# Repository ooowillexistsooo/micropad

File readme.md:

# micropad

the silly little micropad

## bill of materials
- 4 keys
- 4 keycaps
- pcb <3 ofc
- the board attatchment thing
- [the complete bom](production/bom.csv)

## where the things are
- the gerbers are in production/gerbils
- gerber zip is production/gerbils/gerbils.zip
- firmware is in production/firmware (obviously)
- the print file is production/cad/3d-print-this.stl
- the step file is production/cad/hackpad-XD.step (i hope)

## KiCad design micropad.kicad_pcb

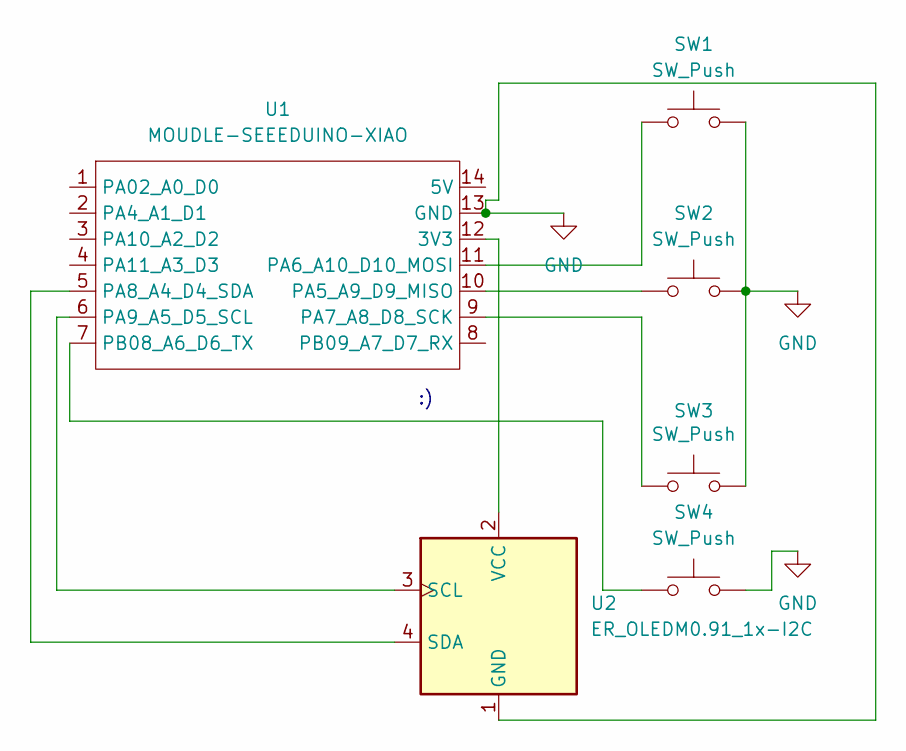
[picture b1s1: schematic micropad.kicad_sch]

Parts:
SW1, SW2, SW3, SW4: SW_Push; SW_Cherry_MX_1.00u_PCB
U1: MOUDLE-SEEEDUINO-XIAO; XIAO-Generic-Hybrid-14P-2.54-21X17.8MM
U2: ER_OLEDM0.91_1x-I2C

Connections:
GND: SW1.2, SW2.2, SW3.2, SW4.2, U1.13 (GND), U2.1 (GND)
unnamed: U1.12 (3V3), U2.2 (VCC)
unnamed: SW2.1, U1.10 (PA5_A9_D9_MISO)
unnamed: SW1.1, U1.11 (PA6_A10_D10_MOSI)
unnamed: SW3.1, U1.9 (PA7_A8_D8_SCK)
unnamed: U1.5 (PA8_A4_D4_SDA), U2.4 (SDA)
unnamed: U1.6 (PA9_A5_D5_SCL), U2.3 (SCL)
unnamed: SW4.1, U1.7 (PB08_A6_D6_TX)

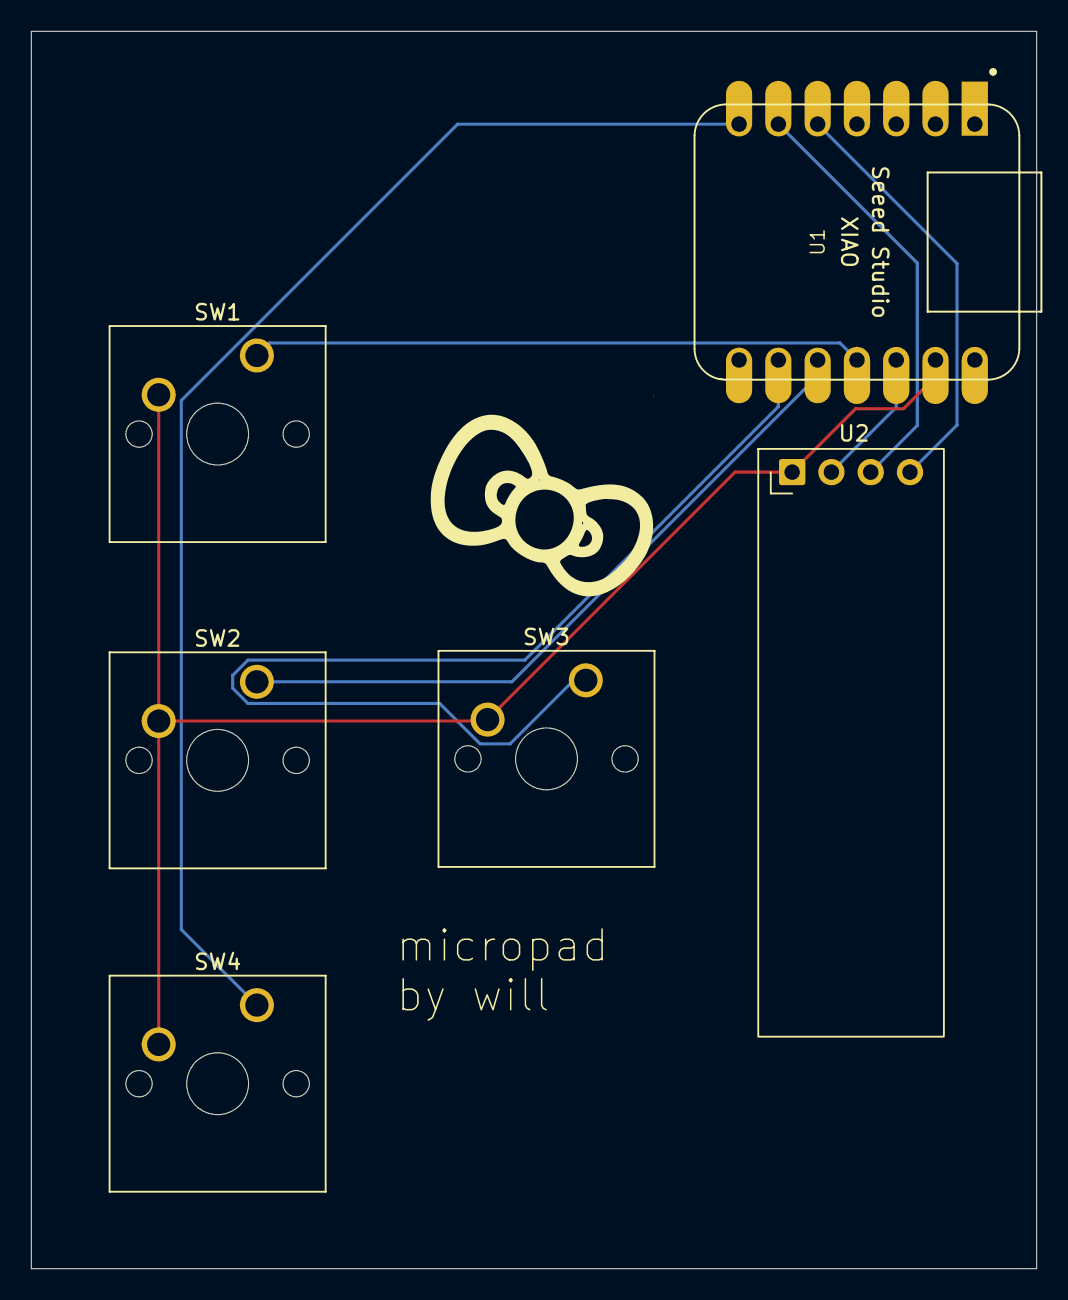
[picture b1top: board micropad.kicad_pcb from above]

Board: 2 copper layers, 65.0 x 80.0 mm, 6 parts (0 on the bottom side), 8 nets.
